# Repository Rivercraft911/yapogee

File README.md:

# Yapogee

Welcome, welcome, welcome! I went looking for a small, affordable QPSK transmitter and couldn't find what I wanted. So we're making one. Meet Yapogee: a little USB-C/SPI board that is ready to yap.

The plan: RP2350B handles DVB-S2 encoding and, through the power of PIO, sends I/Q samples to an AFE7071. A shared reference, LMX2572 LO and optional small driver get us to RF. IREC at 1.28 GHz comes first; 2.4 GHz satellite work reuses the core with a different external PA and filter.

Dashed lines are assembly options. GPIO28 feeds the AFE through the SN65LVDM31DR capture target: DDR at 32/64 MHz for 8/16 Msym/s with four samples per symbol. Loaded timing, startup and power-loss behavior still need verification. See the [dev-board guide](hardware/devboard/README.md).

For N samples per symbol, `f_IQ = N × R_s` and the interleaved bus runs at `f_bus = 2 × f_IQ`. The intended interface is continuous PIO + DDR: at SYS128 and N=4, 8/16 Msym/s uses 32/64 MHz DACCLK and 64/128 Mwords/s. Clock and data writers start atomically. This costs one internal state machine and two instructions, with no added phase hardware. PWM remains a same-pin experiment; module firmware and loaded AFE operation are unqualified.

| Area | Contents |
|---|---|
| [Hardware](hardware/README.md) | Initial dev board, future transmitter board and hardware models |
| [Software](software/README.md) | Data path, timing, reference models and future cleaned firmware |

Schematic capture is underway in [KiCad](hardware/devboard/board/Yapogee-Devboard/Yapogee-Devboard.kicad_pro), with a local [component library](hardware/libraries/README.md). Firmware will come from a cleaned import of the [digital benchmark](https://github.com/Rivercraft911/RP2350_IQ_Benchmark). The RF board hasn't been built yet.

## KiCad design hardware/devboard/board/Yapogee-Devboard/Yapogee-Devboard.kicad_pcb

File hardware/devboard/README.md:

# Yapogee Rev A

RP2350B makes I/Q samples; AFE7071 turns them into RF using the LMX2572 LO. A shared 12 MHz reference ties the timing together. GRF2013 adds optional low-power drive, with the mission PA and band filter outside the board. IREC at 1.28 GHz comes first; the core also covers 2.4 GHz.

[Editable diagrams](architecture/architecture.drawio) · [Clocks](architecture/reference-clocks.svg) · [Power tree](architecture/power-interfaces.svg)

The clock diagram shows the intended DDR interface; the dashed GPIO16/CLK_IO connection is a retained dual-input fallback.

## Parts

| Function | Current device |
|---|---|
| MCU / flash | RP2350B A4 (SC1510-A4), W25Q128JVSIQ; [RP2350 hardware guide](https://datasheets.raspberrypi.com/rp2350/hardware-design-with-rp2350.pdf) |
| Reference / fanout | ECS-TXO-2520MV-120-AN-TR, LMK1C1104PWR |
| DAC / IQ modulator | [AFE7071IRGZT](https://www.ti.com/product/AFE7071) |
| LO | [LMX2572RHAT](https://www.ti.com/lit/ds/symlink/lmx2572.pdf) |
| DAC clock | GPIO28 continuous PIO → SN65LVDM31DR on AFE3V3; intended DDR32/64 MHz |
| RF driver | GRF2013, optional |
| Input | GCT USB4105-GF-A-060, TPS25940ARVCR eFuse |
| Buck | TPS62441QWRQRRQ1: DIG3V3 and PRE2V5 |
| Quiet supplies | TPS7A8801QRTJRQ1: AFE3V3 / AFE1V8; 2×TPS7A2133PQWDRBRQ1: LO3V3 / REF3V3 |
| Reset / watchdog | TPS386000RGPT planned, not captured; RGPR differs only in reel quantity |
| RF driver supply | TPS22810TDBVRQ1 load switch; separate from DAC-clock enable |

This first PCB is also the compact Yapogee module. Castellated contacts and small top-side solder pads provide carrier attachment and bring-up access. Contact layout and underside clearance are still open. These are the working parts, not a released BOM. The [KiCad project](board/Yapogee-Devboard/Yapogee-Devboard.kicad_pro) loads the local [symbols, footprints and models](../libraries/README.md). Capture is underway; layout and hardware testing are still ahead.

## How it fits together

**Power:** USB-C or EXT_5V → eFuse → protected 5 V. The dual buck makes DIG3V3 and PRE2V5; PRE2V5 feeds the AFE's 1.8 V LDO. The three quiet 3.3 V outputs come from protected 5 V. Reset/watchdog and clock interlocks remain to capture; AFE LDO power-good alone does not qualify clock permission. Rail test points and the eFuse current signal support bring-up.

Use a verified 5 V / 3 A source for this eval board. The eFuse retries automatically; reverse-polarity protection is not provided. Each CC pin has a 5.1 kΩ pull-down; available USB current is not detected. A removable solder bridge disconnects USB VBUS when EXT_5V powers the board.

**MCU:** SPI carries payload data; USB handles programming and test access. The benchmark uses GPIO17 SCK, 18 MOSI, 19 CS_N and 22 READY; the board interface is still being captured. SWD, BOOTSEL, RUN and LEDs support bring-up, with isolated I/Q pads planned.

**LO and clocks:** keep the 12 MHz TCXO/LMK1C1104 fanout and full LMX2572. At SYS128, 8/16 Msym/s at four SPS uses DDR32/64 MHz on GP28 and 64/128 Mword/s on the bus. Start the independent PIO clock and writers atomically; the AFE FIFO is bypassed and CLK_IO stays unused in DDR. Preserve CLK_IO and optional GP16/HSTX links for bring-up, with one clock source fitted. PWM remains a same-GP28 trial. Loaded timing, startup, power loss and jitter remain to verify. External reference/LO injection and the LO pad/filter remain assembly options.

**Clock support:** capture the SN65's 100 Ω termination before two 10 nF coupling caps, 1 kΩ across the AFE clock pins after them, disabled-source prebias and DNP damping pads. Use a separate default-off clock request/interlock; `DRIVER_EN` controls the GRF supply. The receiver network and interlock are intended evaluation circuitry, not qualified hardware. Recount AFE3V3 current with the SN65 before freezing the BOM; CDCE and its dedicated I²C isolation remain omitted.

**IQ and RF:** assembly links select raw AFE output or the GRF2013 driver. Populate one top-mounted SMA first; the compact external-LO connector stays DNP. Leave space for a removable shield and accessible bodge pads. Castellated edges attach the module to its carrier; the outline and contact assignments are still open.

The project separates USB, RF/LO, clocks, I/Q, SPI, flash, power and sensitive analog nets. Impedance intent is 90 Ω differential for USB and 50 Ω for RF/LO and controlled CMOS routes; the conditional DAC-clock pair has its own 100 Ω class. Geometry awaits the stackup. CMOS source damping is separate from trace impedance.

## Models

Run from the repo root with Python 3:

```sh
python3 hardware/simulations/link_budget.py
python3 hardware/simulations/reference_lo_loop_screen.py
python3 hardware/simulations/dac_clock_budget.py
```

The link model writes tables and JSON to `hardware/simulations/output/`; the other two print JSON. The DAC-clock calculator covers the retained dual-input SDR/FIFO model. These calculations do not establish DDR startup, measured RF performance or loaded clock timing.

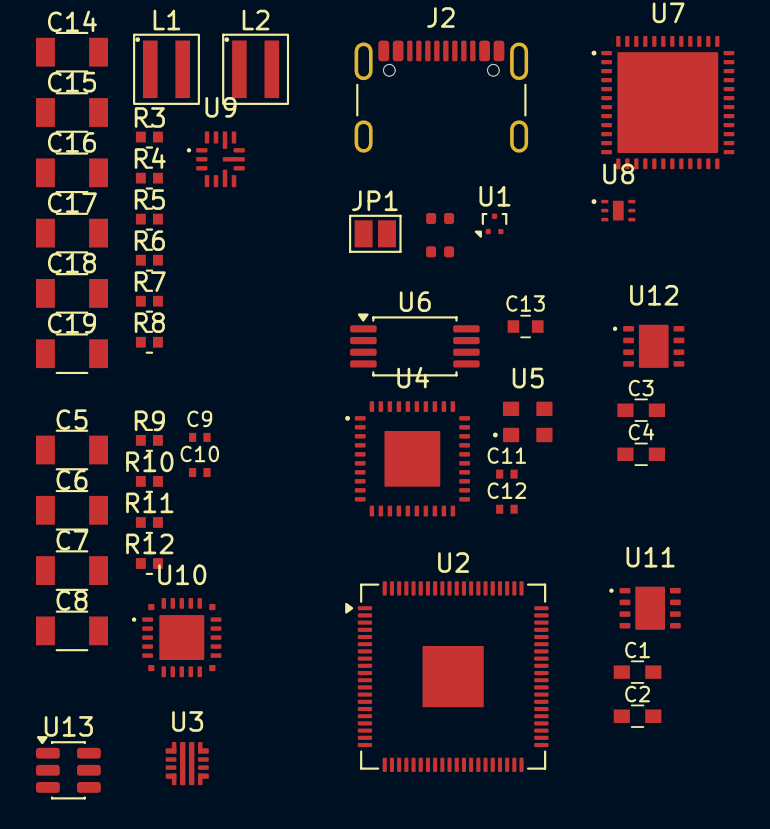
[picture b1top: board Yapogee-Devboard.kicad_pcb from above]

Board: 2 copper layers, 48 parts (0 on the bottom side), 26 nets, no tracks yet.

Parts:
C1, C2, C3, C4: 2.2uF; C_Kyocera_KAM15_1608_RefReflow
C5, C6, C7, C8, C14, C15, C16, C17, C18, C19: 22uF; C_Murata_GCM31_3216_RefReflow
C9, C10, C11, C12: 100nF; C_Murata_GCM15_1005_RefReflow
C13: 1uF; C_Murata_GCM18_1608_RefReflow
J2: USB4105-GF-A
JP1: USB_PWR_LINK; SolderJumper-2_P1.3mm_Open_Pad1.0x1.5mm
L1, L2: 0.68uH; Coilcraft_XGL3520_RefReflow
R1, R2: 5.1kΩ; R_0402
R3, R4: 12kΩ; R_Vishay_TNPW0402_RefReflow
R5, R11: 30kΩ; R_Vishay_TNPW0402_RefReflow
R6, R9, R10: 24kΩ; R_Vishay_TNPW0402_RefReflow
R7: 20kΩ; R_Vishay_TNPW0402_RefReflow
R8: 18kΩ; R_Vishay_TNPW0402_RefReflow
R12: 75kΩ; R_Vishay_TNPW0402_RefReflow
U1: TPD2EUSB30DRTR
U2: RP2350B_SC1510_A4; RP2350B_QFN80_R4S1_Lands
U3: TPS259470ARPWR; TPS259470LRPWR
U4: LMX2572RHAT; TI_RHA0040Y_VQFN-40_6x6mm_P0.5mm_EP3.1x3.1mm
U5: ECS-TXO-2520MV-120-AN-TR; ECS_TXO-2520MV_4Pin_2.5x2.0mm
U6: LMK1C1104PWR; TSSOP-8_4.4x3mm_P0.65mm
U7: AFE7071IRGZT; TI_RGZ0048D_VQFN-48_7x7mm_P0.5mm_EP5.6x5.6mm
U8: GRF2013; GRF_DFN-6_1.5x1.5mm_P0.5mm_EP0.6x1.1mm
U9: TPS62441QWRQRRQ1; TI_RQR0014A_VQFN-HR-14_2.3x2.7mm
U10: TPS7A8801QRTJRQ1; TI_RTJ0020J_WQFN-20-1EP_4x4mm
U11, U12: TPS7A2133PQWDRBRQ1; TI_DRB0008J_VSON-8-1EP_3x3mm
U13: TPS22918DBVR

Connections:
2V5: C18.1, C19.1, L2.2, R8.1
3V3_LO: C2.1, U11.1 (OUT)
3V3_REF: C4.1, C11.1, C12.1, C13.1, U5.4 (VDD), U6.2 (1G), U6.6 (VDD), U12.1 (OUT)
/Power/1V8_3V3_LDO/2V5_IN: C6.1, U10.4 (IN2), U10.5 (IN2), U10.6 (EN2)
/Power/1V8_3V3_LDO/VSYS_IN: C1.1, C3.1, C5.1, C14.1, C15.1, U3.6 (OUT), U9.5 (MODE/SYNC), U9.7 (VIN1), U9.8 (EN1), U9.10 (EN2), U9.11 (VIN2), U10.1 (IN1), U10.2 (IN1), U10.20 (EN1), U11.5 (EN), U11.8 (IN), U12.5 (EN), U12.8 (IN)
/Power/5V_IN: JP1.2 (B), U3.5 (IN)
AFE_1V8: C8.1, R11.2, U10.11 (OUT2), U10.12 (OUT2)
AFE_3V3: C7.1, R12.2, U10.14 (OUT1), U10.15 (OUT1)
DIG_3V3: C16.1, C17.1, L1.2, R6.2
GND: C1.2, C2.2, C3.2, C4.2, C5.2, C6.2, C7.2, C8.2, C9.1, C10.1, C11.2, C12.2, C13.2, C14.2, C15.2, C16.2, C17.2, C18.2, C19.2, J2.A1 (GND), J2.A12 (GND), J2.B1 (GND), J2.B12 (GND), J2.SH (SHIELD), R1.2, R2.2, R3.2, R4.2, R9.1, R10.1, U1.3 (GND), U2.61 (VREG_AVDD), U2.62 (VREG_PGND), U2.81 (GND), U5.2 (GND), U6.4 (GND), U9.2 (GND), U9.9 (GND), U10.3 (GND), U10.8 (SS_CTRL2), U10.13 (GND), U10.18 (SS_CTRL1), U10.21 (EP_GND), U11.4 (GND), U11.9 (EP_GND), U12.4 (GND), U12.9 (EP_GND)
unnamed: J2.A5 (CC1), R1.1
unnamed: J2.B5 (CC2), R2.1
unnamed: J2.A4 (VBUS), J2.A9 (VBUS), J2.B4 (VBUS), J2.B9 (VBUS), JP1.1 (A)
unnamed: R5.2, R6.1
unnamed: R7.2, R8.2
unnamed: J2.A6 (D+), J2.B6 (D+), U1.1 (D+)
unnamed: J2.A7 (D-), J2.B7 (D-), U1.2 (D-)
unnamed: U5.3 (OUT), U6.1 (CLKIN)
unnamed: R4.1, R5.1, U9.3 (FB1)
unnamed: R3.1, R7.1, U9.1 (FB2)
unnamed: L1.1, U9.6 (SW1)
unnamed: L2.1, U9.12 (SW2)
unnamed: R9.2, R12.1, U10.16 (FB1)
unnamed: R10.2, R11.1, U10.10 (FB2)
unnamed: C10.2, U10.19 (NR/SS1)
unnamed: C9.2, U10.7 (NR/SS2)
